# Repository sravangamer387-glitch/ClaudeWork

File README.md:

# ClaudeWork – gravity toys, electronic toys, DJ system, prototypes

| Folder | What | Start here |
|---|---|---|
| `gravity-toys/` | Research, 5 gravity-toy designs, laser-cut files, physics verification, business launch pack | `README.md` |
| `electronics-toys/` | Top-50 electronic toys for India (phases 1–6), shared audio platform firmware/hardware/enclosures | `README.md`, `wave1/README.md` |
| `dj-setup/` | Portable DJ / party system project plan (market, architecture, compliance, phased plan) | `README.md` |
| `proposals/` | The proposals that were approved and built (see `products/`) | `next-portfolio-proposal.md` |
| `products/` | Six built products (games, automata, STEM kit, tank controller, irrigation controller, LPG alarm design study) with decisions and handoff | `README.md`, `DECISIONS.md`, `HANDOFF.md` |
| `toys10/` | Ten new toys with tested engines, simulations, cut files, docs | `README.md` |
| `utility10/` | Ten utility tools (8 electronics, 2 laser-cut) with tested engines, SVG/DXF files, enclosures, docs | `README.md` |
| `prototypes/` | Build packs for ten prototypes, each under Rs 3,000, with firmware that compiles for Arduino Nano | `README.md` |

Everything is mirrored to Google Drive folders "Gravity Toys", "Electronics Toys", "DJ Setup" (documents and data tables). Source code, STL and PNG files live in this repo only.

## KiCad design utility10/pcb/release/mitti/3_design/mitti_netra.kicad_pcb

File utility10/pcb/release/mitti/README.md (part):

# MITTI-NETRA soil and structure telemetry node (ESP32-S3 + LTE-M modem socket) (rev A)

MITTI-NETRA soil and structure telemetry node (90 x 80 mm): ESP32-S3, TP4056 solar/USB charger for one Li-ion cell, 3.3 V LDO, switched socket for a SIM7080G breakout, ADXL345, HX711 strain input, soil-probe and DS18B20 inputs.

**Status: engineering release, software-verified only (ERC on the netlist, KiCad DRC, netlist cross-check, SPICE where noted). Not yet built, not reviewed by a second engineer, not certified.**

## Specification
- Board 90 x 80 mm, 2 layers, 1.6 mm FR-4, 1 oz copper, rounded corners R2.5 mm, 3 x M2.5 mounting holes, 2 fiducials.
- Rules used: min track 0.2 mm (power 0.4 mm), min clearance 0.15 mm, via 0.6/0.3 mm, GND pour on both layers, 212 stitching vias.
- Finish: ENIG recommended (HASL lead-free acceptable); green mask, white silk; IPC class 2.
- 62 parts, 41 nets.

## Circuit description
- **Charging:** solar (JST-PH 2) and USB VBUS OR-ed by SS14 diodes into a TP4056 with PROG = 2.2 k (about 0.58 A); a protected 1S Li-ion cell on JST-PH 2 (no protection IC on the board).
- **Rails:** AP2112K 3.3 V from the cell (stops regulating near 3.55 V); modem VBAT through an AO3401A high-side switch driven by an AO3400A, with 100 uF + 22 uF burst capacitors.
- **Sensors:** ADXL345 on I2C (address 0x53, INT1 wakes the MCU); HX711 (as on Gas Taraju) for a strain bridge; capacitive soil probe through 1 k + 100 nF to an ADC pin; DS18B20 on 1-Wire.

## Power
Target under 100 uA in deep sleep with the modem off (not measured); modem bursts up to about 0.5 A while transmitting.

## Verification
| Check | Result |
|---|---|
| Electrical rule check on the netlist (own ERC: unconnected pins, single-pin nets, output conflicts, unpowered supplies, symbol/footprint pin match) | 0 errors, 0 warnings |
| KiCad DRC | 0 errors, 0 warnings; unconnected pads: 0 |
| Schematic netlist equals PCB netlist | NO: {"[('D2', '2'), ('J1', 'A4'), ('J1', 'A9')]...": 'only in PCB', "[('D2', '1'), ('J1', 'A4'), ('J1', 'A9')]...": 'only in schematic', "[('C1', '1'), ('D1', '1'), ('D2', '1')]...": 'only in PCB', "[('D1', '1'), ('J2', '1')]...": 'only in schematic', "[('D1', '2'), ('J2', '1')]...": 'only in PCB', "[('C1', '1'), ('D1', '2'), ('D2', '2')]...": 'only in schematic'} |
| Router failures | 0 |
| 3D STEP export | yes |
| Independent Gerber parse (gerbonara): layers parsed, outline size equals the design | 9 layers, outline [90.1, 80.1] mm, match |

Enclosure (prototype shell for 3D printing): outer 95.2 x 85.2 x 20.6 mm, collision/opening check: pass

## Bill of materials
| Ref | Value | Footprint | Manufacturer part | LCSC # | LCSC status |
|---|---|---|---|---|---|
| U1 | ESP32-S3-WROOM-1-N8 | ESP32-S3-WROOM-1 | ESP32-S3-WROOM-1-N8 | C2913198 | verified |
| C37 | 100n | C_0603_1608Metric | Samsung CL10B104KB8NNNC 0603 100nF X7R 50V | C1591 | verified |
| C38 | 10u | C_0805_2012Metric | 0805 10uF X5R | C15850 | verified |
| R42 | 10k | R_0603_1608Metric | 0603 10k 1% | C25804 | verified |
| C39 | 1u | C_0603_1608Metric | 0603 1uF X7R | C15849 | verified |
| SW2 | Reset (EN) | SW_SPST_B3U-1000P | Omron B3U-1000P | C231329 | verified |
| SW3 | Boot (IO0) | SW_SPST_B3U-1000P | Omron B3U-1000P | C231329 | verified |
| J1 | USB-C (charge + program) | USB_C_Receptacle_HRO_TYPE-C-31-M-12 | TYPE-C-31-M-12 | C165948 | verified |
| R43 | 5.1k | R_0603_1608Metric | 0603 5.1k 1% | C23186 | verified |
| R44 | 5.1k | R_0603_1608Metric | 0603 5.1k 1% | C23186 | verified |
| J2 | Solar panel 5-6 V | JST_PH_B2B-PH-K_1x02_P2.00mm_Vertical | JST B2B-PH-K-S(LF)(SN) | C131337 | verified |
| D1 | SS14 | D_SMA | SS14 | C84343 | verified |
| D2 | SS14 | D_SMA | SS14 | C84343 | verified |
| C1 | 10u | C_0805_2012Metric | 0805 10uF X5R | C15850 | verified |
| U4 | TP4056 | HSOP-8-1EP_3.9x4.9mm_P1.27mm_EP2.41x3.1mm | TPOWER TP4056 | C382139 | verified |
| R1 | 2.2k | R_0603_1608Metric | 0603 2.2k 1% | C4190 | verified |
| C2 | 10u | C_0805_2012Metric | 0805 10uF X5R | C15850 | verified |
| D3 | Red | LED_0603_1608Metric | Hubei KENTO KT-0603R red (Everlight 19-217 was out of stock) | C2286 | verified |
| R2 | 1k | R_0603_1608Metric | 0603 1k 1% | C21190 | verified |
| D4 | Green | LED_0603_1608Metric | Hubei KENTO KT-0603YG yellow-green 570 nm, Vf about 2 V (lights well from 3.3 V with 1 k; the Everlight 19-217 green was out of stock) | C2289 | verified |
| R3 | 1k | R_0603_1608Metric | 0603 1k 1% | C21190 | verified |
| J3 | Li-ion cell (protected!) | JST_PH_B2B-PH-K_1x02_P2.00mm_Vertical | JST B2B-PH-K-S(LF)(SN) | C131337 | verified |
| U3 | AP2112K-3.3 | SOT-23-5 | AP2112K-3.3TRG1 | C51118 | verified |
| C3 | 1u | C_0603_1608Metric | 0603 1uF X7R | C15849 | verified |
| C4 | 10u | C_0805_2012Metric | 0805 10uF X5R | C15850 | verified |
| R4 | 330k | R_0603_1608Metric | UNI-ROYAL 0603WAF3303T5E | C23137 | verified |
| R5 | 330k | R_0603_1608Metric | UNI-ROYAL 0603WAF3303T5E | C23137 | verified |
| C5 | 100n | C_0603_1608Metric | Samsung CL10B104KB8NNNC 0603 100nF X7R 50V | C1591 | verified |
| Q1 | AO3401A | SOT-23 | AO3401A | C15127 | verified |
| R6 | 100k | R_0603_1608Metric | 0603 100k 1% | C25803 | verified |
| Q2 | AO3400A | SOT-23 | AO3400A | C20917 | verified |
| R7 | 100 | R_0603_1608Metric | UNI-ROYAL 0603WAF1000T5E | C22775 | verified |
| R8 | 100k | R_0603_1608Metric | 0603 100k 1% | C25803 | verified |
| C6 | 100u/35V | CP_Elec_6.3x7.7 | Lelon VZH101M1VTR-0607 | C176683 | verified |
| C7 | 22u/10V | C_0805_2012Metric | Samsung CL21A226MPQNNNE | C29277 | verified |
| J6 | Cellular modem (SIM7080G breakout) | PinHeader_2x03_P2.54mm_Vertical | HCTL PZ254-2-03-Z-8.5 | C2894964 | verified |
| U5 | ADXL345 | LGA-14_3x5mm_P0.8mm_LayoutBorder1x6y | ADXL345BCCZ-RL7 | C9667 | verified |
| C8 | 100n | C_0603_1608Metric | Samsung CL10B104KB8NNNC 0603 100nF X7R 50V | C1591 | verified |
| C9 | 100n | C_0603_1608Metric | Samsung CL10B104KB8NNNC 0603 100nF X7R 50V | C1591 | verified |
| R9 | 4.7k | R_0603_1608Metric | 0603 4.7k 1% | C23162 | verified |
| R10 | 4.7k | R_0603_1608Metric | 0603 4.7k 1% | C23162 | verified |
| U2 | HX711 | SOIC-16_3.9x9.9mm_P1.27mm | HX711 | C43656 | verified |
| R11 | 100 | R_0603_1608Metric | UNI-ROYAL 0603WAF1000T5E | C22775 | verified |
| C10 | 100n | C_0603_1608Metric | Samsung CL10B104KB8NNNC 0603 100nF X7R 50V | C1591 | verified |
| C11 | 100n | C_0603_1608Metric | Samsung CL10B104KB8NNNC 0603 100nF X7R 50V | C1591 | verified |
| C12 | 100n | C_0603_1608Metric | Samsung CL10B104KB8NNNC 0603 100nF X7R 50V | C1591 | verified |
| C13 | 10u | C_0805_2012Metric | 0805 10uF X5R | C15850 | verified |
| R12 | 100 | R_0603_1608Metric | UNI-ROYAL 0603WAF1000T5E | C22775 | verified |
| C14 | 100n | C_0603_1608Metric | Samsung CL10B104KB8NNNC 0603 100nF X7R 50V | C1591 | verified |
| C15 | 100n | C_0603_1608Metric | Samsung CL10B104KB8NNNC 0603 100nF X7R 50V | C1591 | verified |
| J4 | Strain-gauge bridge E+ E- A+ A- | JST_PH_B4B-PH-K_1x04_P2.00mm_Vertical | JST B4B-PH-K-S(LF)(SN) | C131334 | verified |
| J5 | Soil probe (capacitive, 3.3 V) | JST_PH_B3B-PH-K_1x03_P2.00mm_Vertical | JST B3B-PH-K-S(LF)(SN) | C131339 | verified |
| J7 | DS18B20 temp | JST_PH_B3B-PH-K_1x03_P2.00mm_Vertical | JST B3B-PH-K-S | C131339 | verified |
| R13 | 4.7k | R_0603_1608Metric | 0603 4.7k 1% | C23162 | verified |
| R15 | 1k | R_0603_1608Metric | 0603 1k 1% | C21190 | verified |
| C16 | 100n | C_0603_1608Metric | Samsung CL10B104KB8NNNC 0603 100nF X7R 50V | C1591 | verified |
| D5 | Green | LED_0603_1608Metric | Hubei KENTO KT-0603YG yellow-green 570 nm, Vf about 2 V (lights well from 3.3 V with 1 k; the Everlight 19-217 green was out of stock) | C2289 | verified |
| R14 | 1k | R_0603_1608Metric | 0603 1k 1% | C21190 | verified |
| J8 | UART flash/debug (USB-serial adapter) | JST_PH_B3B-PH-K_1x03_P2.00mm_Vertical | JST B3B-PH-K-S(LF)(SN) | C131339 | verified |
| TP1 | TP | TestPoint_Pad_D1.5mm |  |  |  |
| TP2 | TP | TestPoint_Pad_D1.5mm |  |  |  |
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
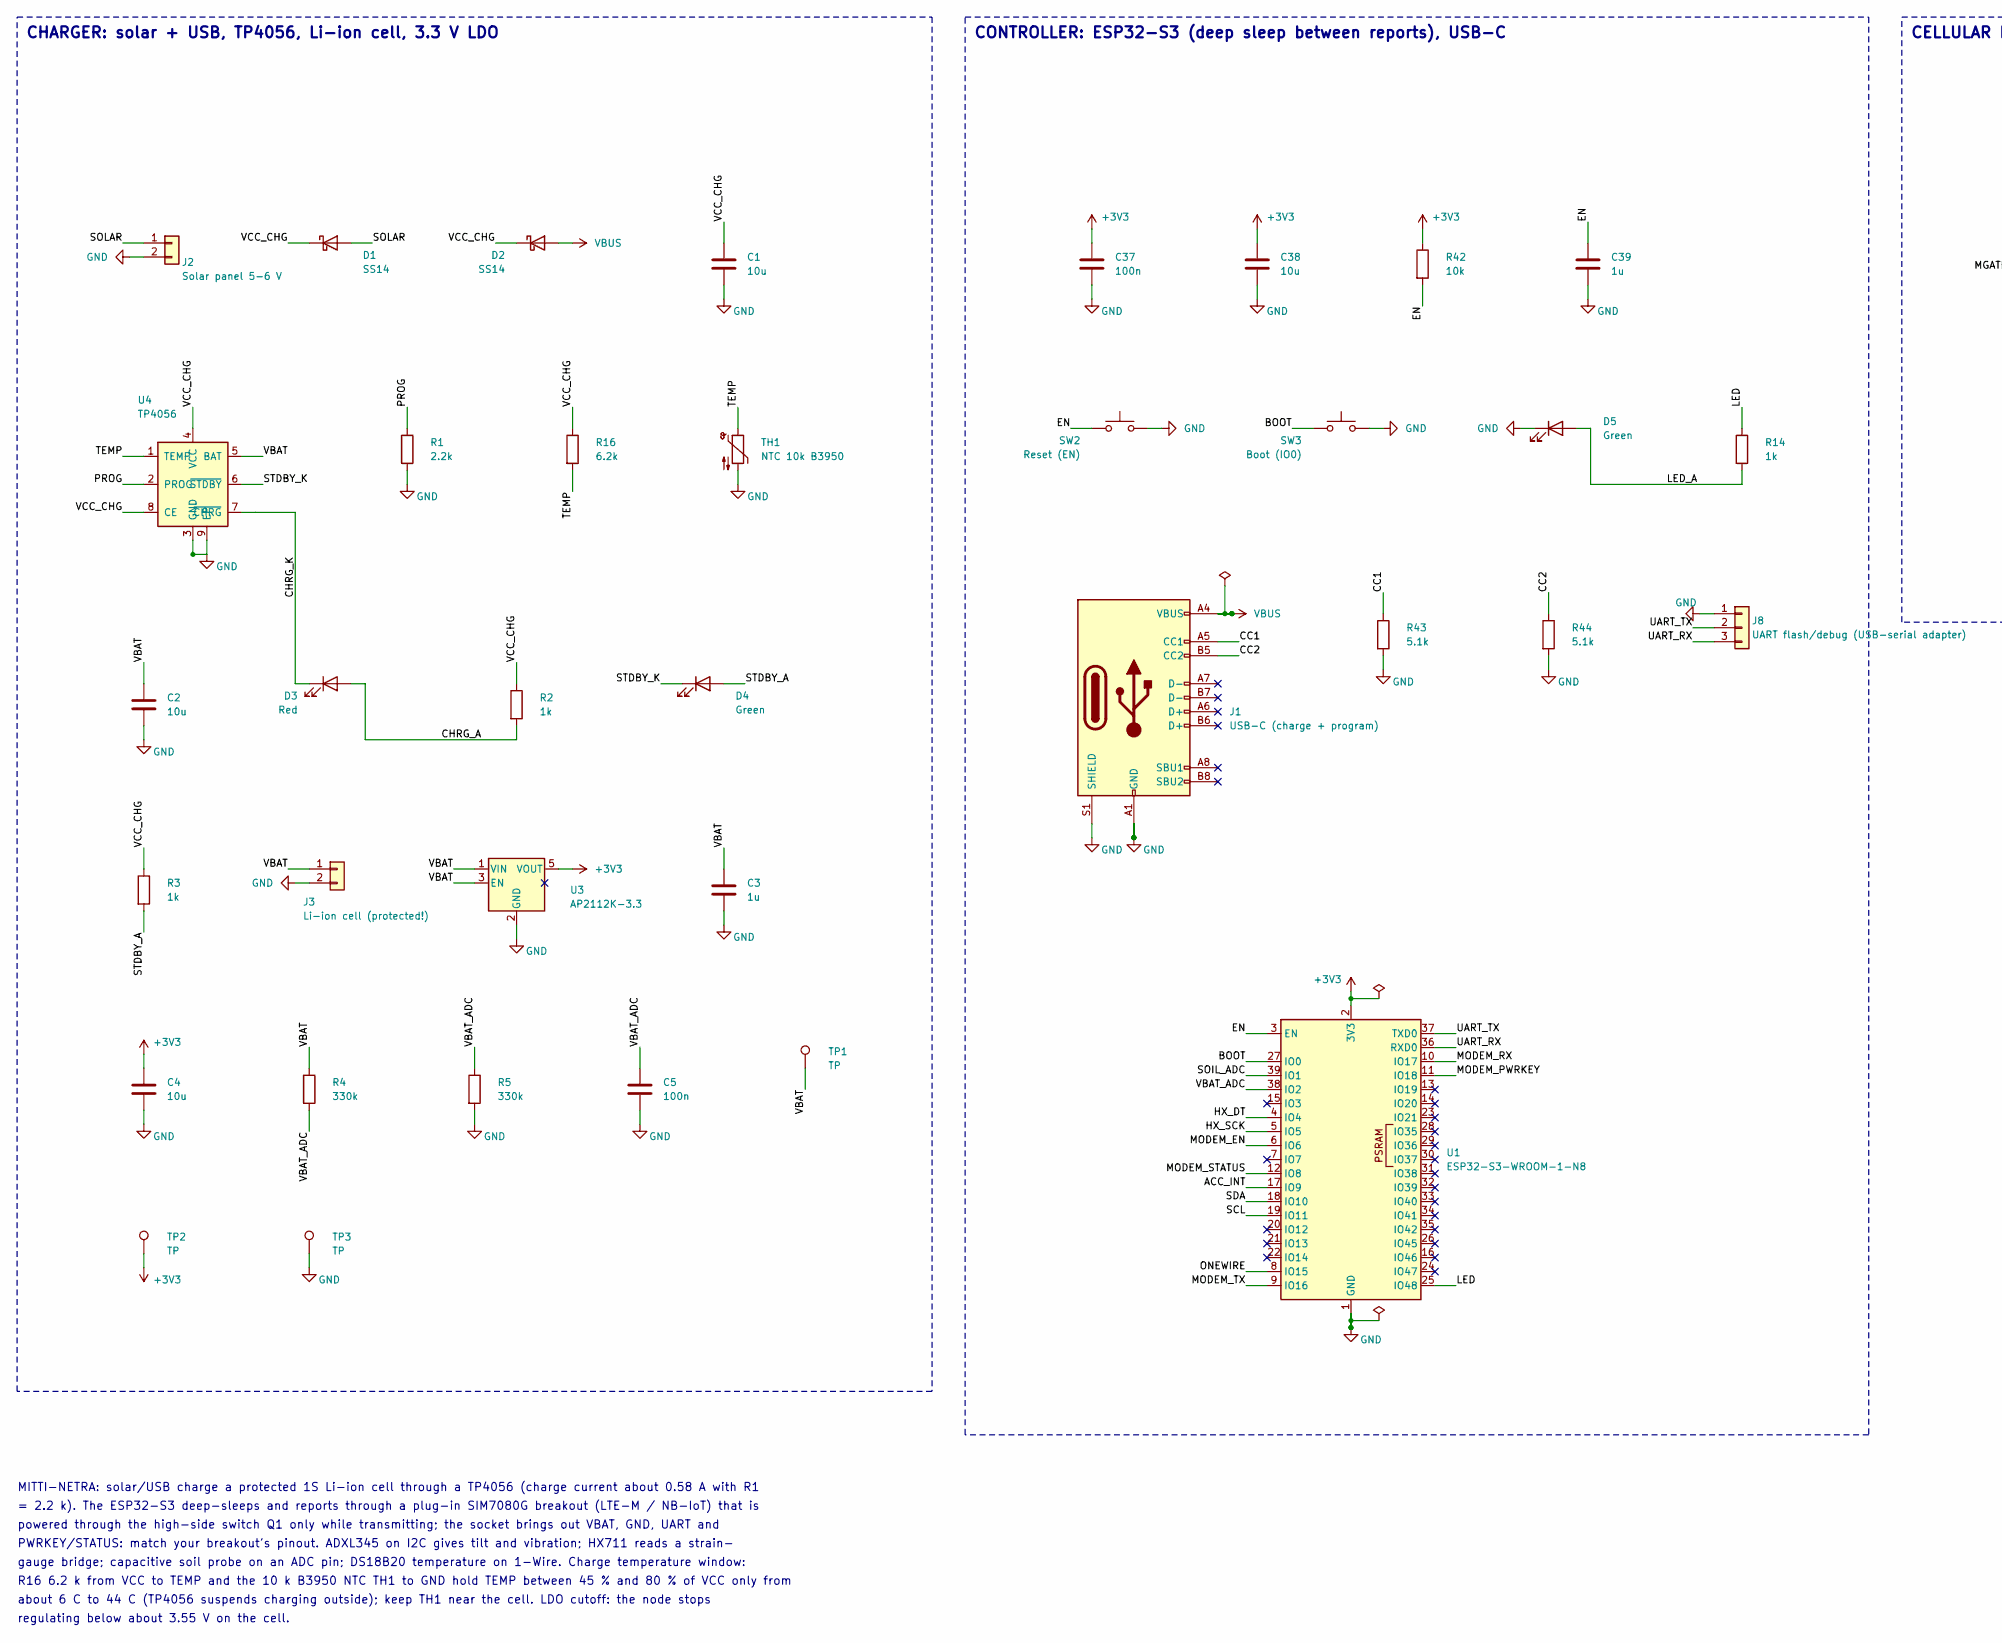
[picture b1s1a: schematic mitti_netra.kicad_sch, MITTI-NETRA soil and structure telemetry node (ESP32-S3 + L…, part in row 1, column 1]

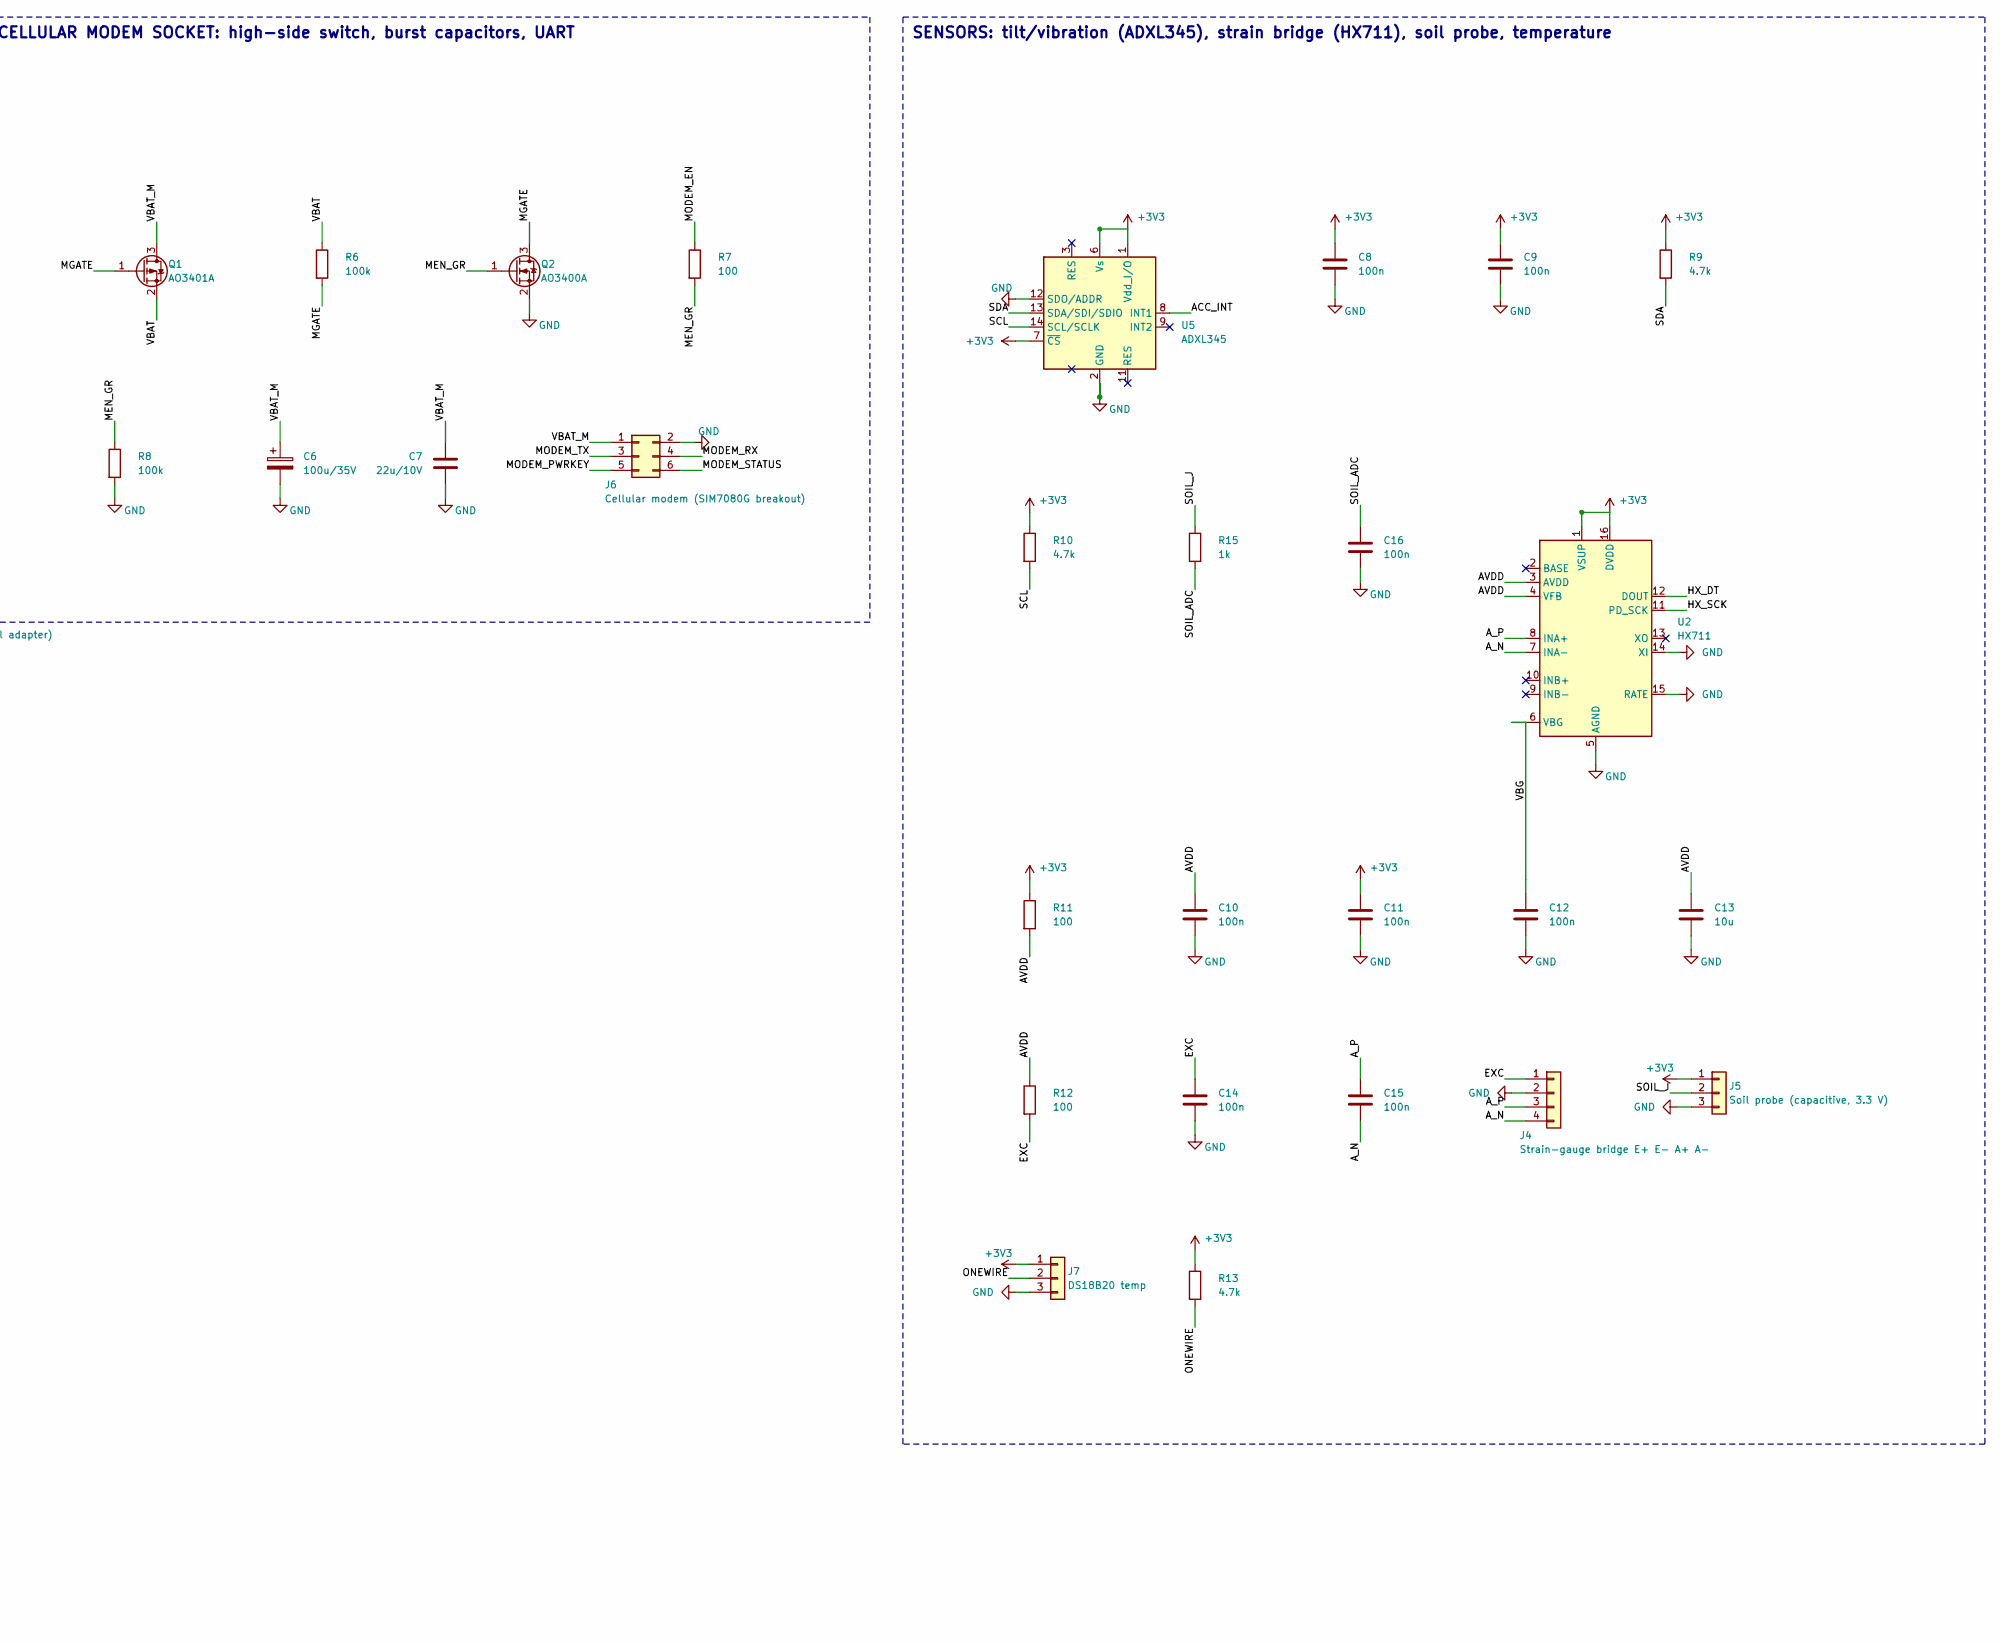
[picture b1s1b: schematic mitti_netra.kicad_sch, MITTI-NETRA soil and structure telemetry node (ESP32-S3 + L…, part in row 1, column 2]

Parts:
C1, C2, C4, C13, C38: 10u; C_0805_2012Metric
C3, C39: 1u; C_0603_1608Metric
C5, C8, C9, C10, C11, C12, C14, C15, C16, C37: 100n; C_0603_1608Metric
C6: 100u/35V; CP_Elec_6.3x7.7
C7: 22u/10V; C_0805_2012Metric
D1, D2: SS14; D_SMA
D3: Red; LED_0603_1608Metric
D4, D5: Green; LED_0603_1608Metric
J1: USB-C (charge + program); USB_C_Receptacle_HRO_TYPE-C-31-M-12
J2: Solar panel 5-6 V; JST_PH_B2B-PH-K_1x02_P2.00mm_Vertical
J3: Li-ion cell (protected!); JST_PH_B2B-PH-K_1x02_P2.00mm_Vertical
J4: Strain-gauge bridge E+ E- A+ A-; JST_PH_B4B-PH-K_1x04_P2.00mm_Vertical
J5: Soil probe (capacitive, 3.3 V); JST_PH_B3B-PH-K_1x03_P2.00mm_Vertical
J6: Cellular modem (SIM7080G breakout); PinHeader_2x03_P2.54mm_Vertical
J7: DS18B20 temp; JST_PH_B3B-PH-K_1x03_P2.00mm_Vertical
J8: UART flash/debug (USB-serial adapter); JST_PH_B3B-PH-K_1x03_P2.00mm_Vertical
Q1: AO3401A; SOT-23
Q2: AO3400A; SOT-23
R1: 2.2k; R_0603_1608Metric
R2, R3, R14, R15: 1k; R_0603_1608Metric
R4, R5: 330k; R_0603_1608Metric
R6, R8: 100k; R_0603_1608Metric
R7, R11, R12: 100; R_0603_1608Metric
R9, R10, R13: 4.7k; R_0603_1608Metric
R16: 6.2k; R_0603_1608Metric
R42: 10k; R_0603_1608Metric
R43, R44: 5.1k; R_0603_1608Metric
SW2: Reset (EN); SW_SPST_B3U-1000P
SW3: Boot (IO0); SW_SPST_B3U-1000P
TH1: NTC 10k B3950; R_0805_2012Metric
TP1, TP2, TP3: TP; TestPoint_Pad_D1.5mm
U1: ESP32-S3-WROOM-1-N8; ESP32-S3-WROOM-1
U2: HX711; SOIC-16_3.9x9.9mm_P1.27mm
U3: AP2112K-3.3; SOT-23-5
U4: TP4056; HSOP-8-1EP_3.9x4.9mm_P1.27mm_EP2.41x3.1mm
U5: ADXL345; LGA-14_3x5mm_P0.8mm_LayoutBorder1x6y

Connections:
+3V3: C4.1, C8.1, C9.1, C11.1, C37.1, C38.1, J5.1, J7.1, R9.1, R10.1, R11.1, R13.1, R42.1, TP2.1, U1.2 (3V3), U2.1 (VSUP), U2.16 (DVDD), U3.5 (VOUT), U5.1 (Vdd_I/O), U5.6 (Vs), U5.7 (~CS)
ACC_INT: U1.17 (IO9), U5.8 (INT1)
AVDD: C10.1, C13.1, R11.2, R12.1, U2.3 (AVDD), U2.4 (VFB)
A_N: C15.2, J4.4, U2.7 (INA-)
A_P: C15.1, J4.3, U2.8 (INA+)
BOOT: SW3.1, U1.27 (IO0)
CC1: J1.A5 (CC1), R43.1
CC2: J1.B5 (CC2), R44.1
CHRG_A: D3.2 (A), R2.2
CHRG_K: D3.1 (K), U4.7 (~CHRG)
EN: C39.1, R42.2, SW2.1, U1.3 (EN)
EXC: C14.1, J4.1, R12.2
GND: C1.2, C2.2, C3.2, C4.2, C5.2, C6.2, C7.2, C8.2, C9.2, C10.2, C11.2, C12.2, C13.2, C14.2, C16.2, C37.2, C38.2, C39.2, D5.1 (K), J1.A1 (GND), J1.A12 (GND), J1.B1 (GND), J1.B12 (GND), J1.S1 (SHIELD), J2.2, J3.2, J4.2, J5.3, J6.2, J7.3, J8.1, Q2.2 (S), R1.2, R5.2, R8.2, R43.2, R44.2, SW2.2, SW3.2, TH1.2, TP3.1, U1.1 (GND), U1.40 (GND), U1.41 (GND), U2.5 (AGND), U2.14 (XI), U2.15 (RATE), U3.2 (GND), U4.3 (GND), U4.9 (EP), U5.2 (GND), U5.4 (GND), U5.5 (GND), U5.12 (SDO/ADDR)
HX_DT: U1.4 (IO4), U2.12 (DOUT)
HX_SCK: U1.5 (IO5), U2.11 (PD_SCK)
LED: R14.1, U1.25 (IO48)
LED_A: D5.2 (A), R14.2
MEN_GR: Q2.1 (G), R7.2, R8.1
MGATE: Q1.1 (G), Q2.3 (D), R6.2
MODEM_EN: R7.1, U1.6 (IO6)
MODEM_PWRKEY: J6.5, U1.11 (IO18)
MODEM_RX: J6.4, U1.10 (IO17)
MODEM_STATUS: J6.6, U1.12 (IO8)
MODEM_TX: J6.3, U1.9 (IO16)
ONEWIRE: J7.2, R13.2, U1.8 (IO15)
PROG: R1.1, U4.2 (PROG)
SCL: R10.2, U1.19 (IO11), U5.14 (SCL/SCLK)
SDA: R9.2, U1.18 (IO10), U5.13 (SDA/SDI/SDIO)
SOIL_ADC: C16.1, R15.2, U1.39 (IO1)
SOIL_J: J5.2, R15.1
SOLAR: D1.2 (A), J2.1
STDBY_A: D4.2 (A), R3.2
STDBY_K: D4.1 (K), U4.6 (~STDBY)
TEMP: R16.2, TH1.1, U4.1 (TEMP)
UART_RX: J8.3, U1.36 (RXD0)
UART_TX: J8.2, U1.37 (TXD0)
VBAT: C2.1, C3.1, J3.1, Q1.2 (S), R4.1, R6.1, TP1.1, U3.1 (VIN), U3.3 (EN), U4.5 (BAT)
VBAT_ADC: C5.1, R4.2, R5.1, U1.38 (IO2)
VBAT_M: C6.1, C7.1, J6.1, Q1.3 (D)
VBG: C12.1, U2.6 (VBG)
VBUS: D2.2 (A), J1.A4 (VBUS), J1.A9 (VBUS), J1.B4 (VBUS), J1.B9 (VBUS)
VCC_CHG: C1.1, D1.1 (K), D2.1 (K), R2.1, R3.1, R16.1, U4.4 (VCC), U4.8 (CE)

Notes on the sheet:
CHARGER: solar + USB, TP4056, Li-ion cell, 3.3 V LDO
CONTROLLER: ESP32-S3 (deep sleep between reports), USB-C
CELLULAR MODEM SOCKET: high-side switch, burst capacitors, UART
SENSORS: tilt/vibration (ADXL345), strain bridge (HX711), soil probe, temperature
MITTI-NETRA: solar/USB charge a protected 1S Li-ion cell through a TP4056 (charge current about 0.58 A with R1
= 2.2 k). The ESP32-S3 deep-sleeps and reports through a plug-in SIM7080G breakout (LTE-M / NB-IoT) that is
powered through the high-side switch Q1 only while transmitting; the socket brings out VBAT, GND, UART and
PWRKEY/STATUS: match your breakout's pinout. ADXL345 on I2C gives tilt and vibration; HX711 reads a strain-
gauge bridge; capacitive soil probe on an ADC pin; DS18B20 temperature on 1-Wire. Charge temperature window:
R16 6.2 k from VCC to TEMP and the 10 k B3950 NTC TH1 to GND hold TEMP between 45 % and 80 % of VCC only from
about 6 C to 44 C (TP4056 suspends charging outside); keep TH1 near the cell. LDO cutoff: the node stops
regulating below about 3.55 V on the cell.

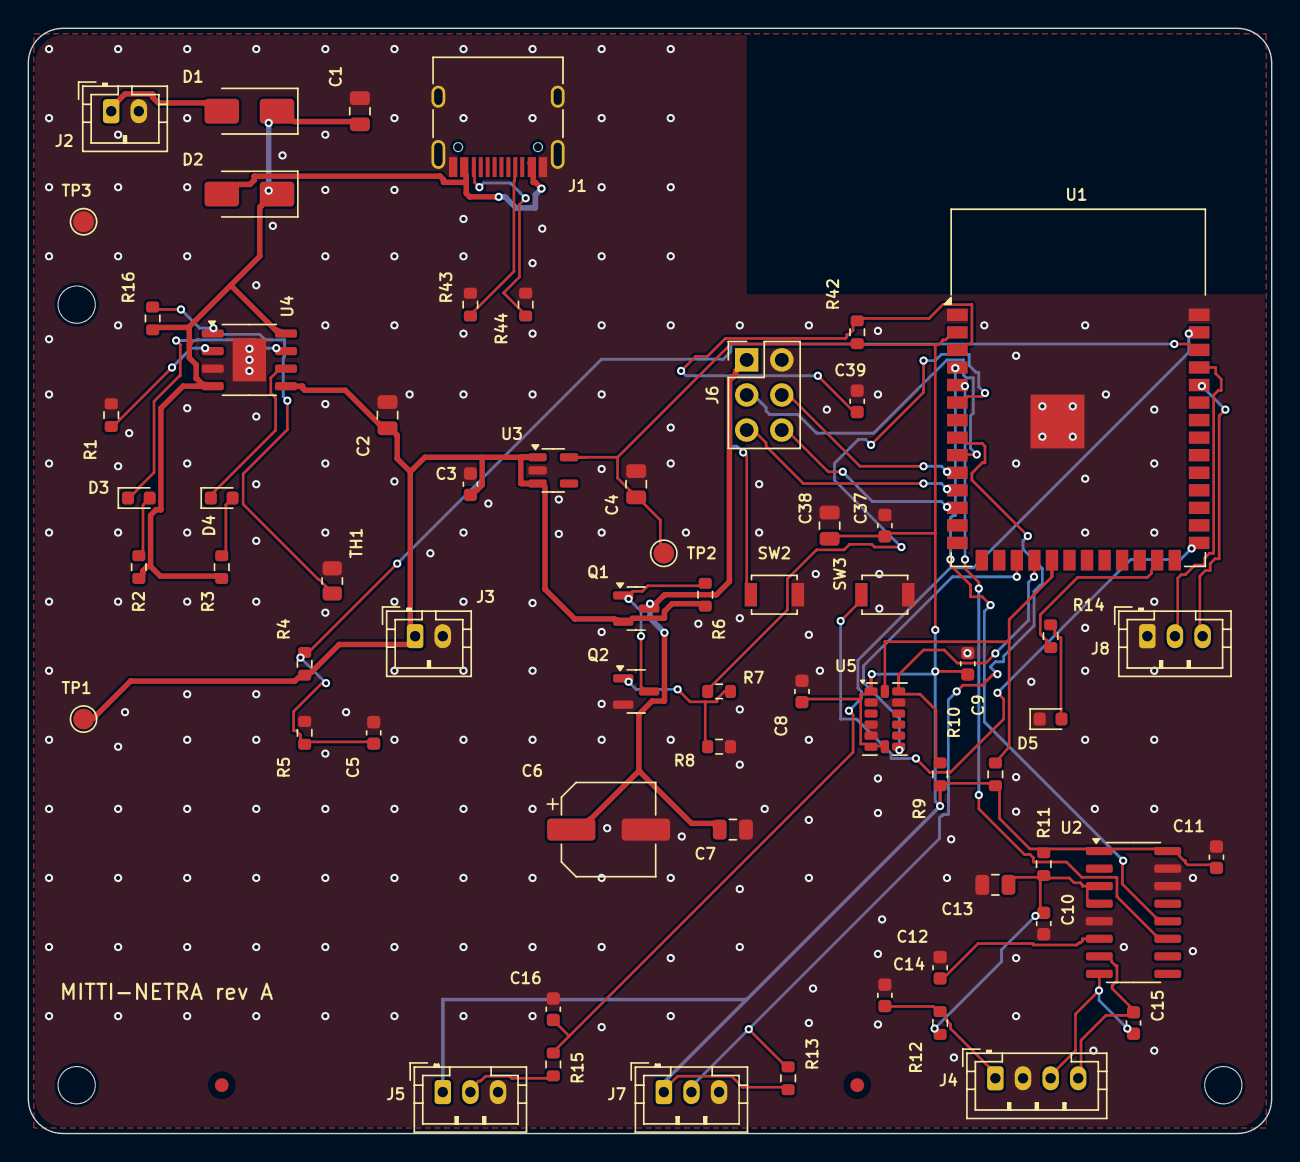
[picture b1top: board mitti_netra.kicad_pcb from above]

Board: 2 copper layers, 90.0 x 80.0 mm, 69 parts (0 on the bottom side), 42 nets.

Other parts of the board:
FID1, FID2: Fiducial; Fiducial_1mm_Mask2mm
H1, H2, H3: M2.5; MountingHole_2.7mm_M2.5

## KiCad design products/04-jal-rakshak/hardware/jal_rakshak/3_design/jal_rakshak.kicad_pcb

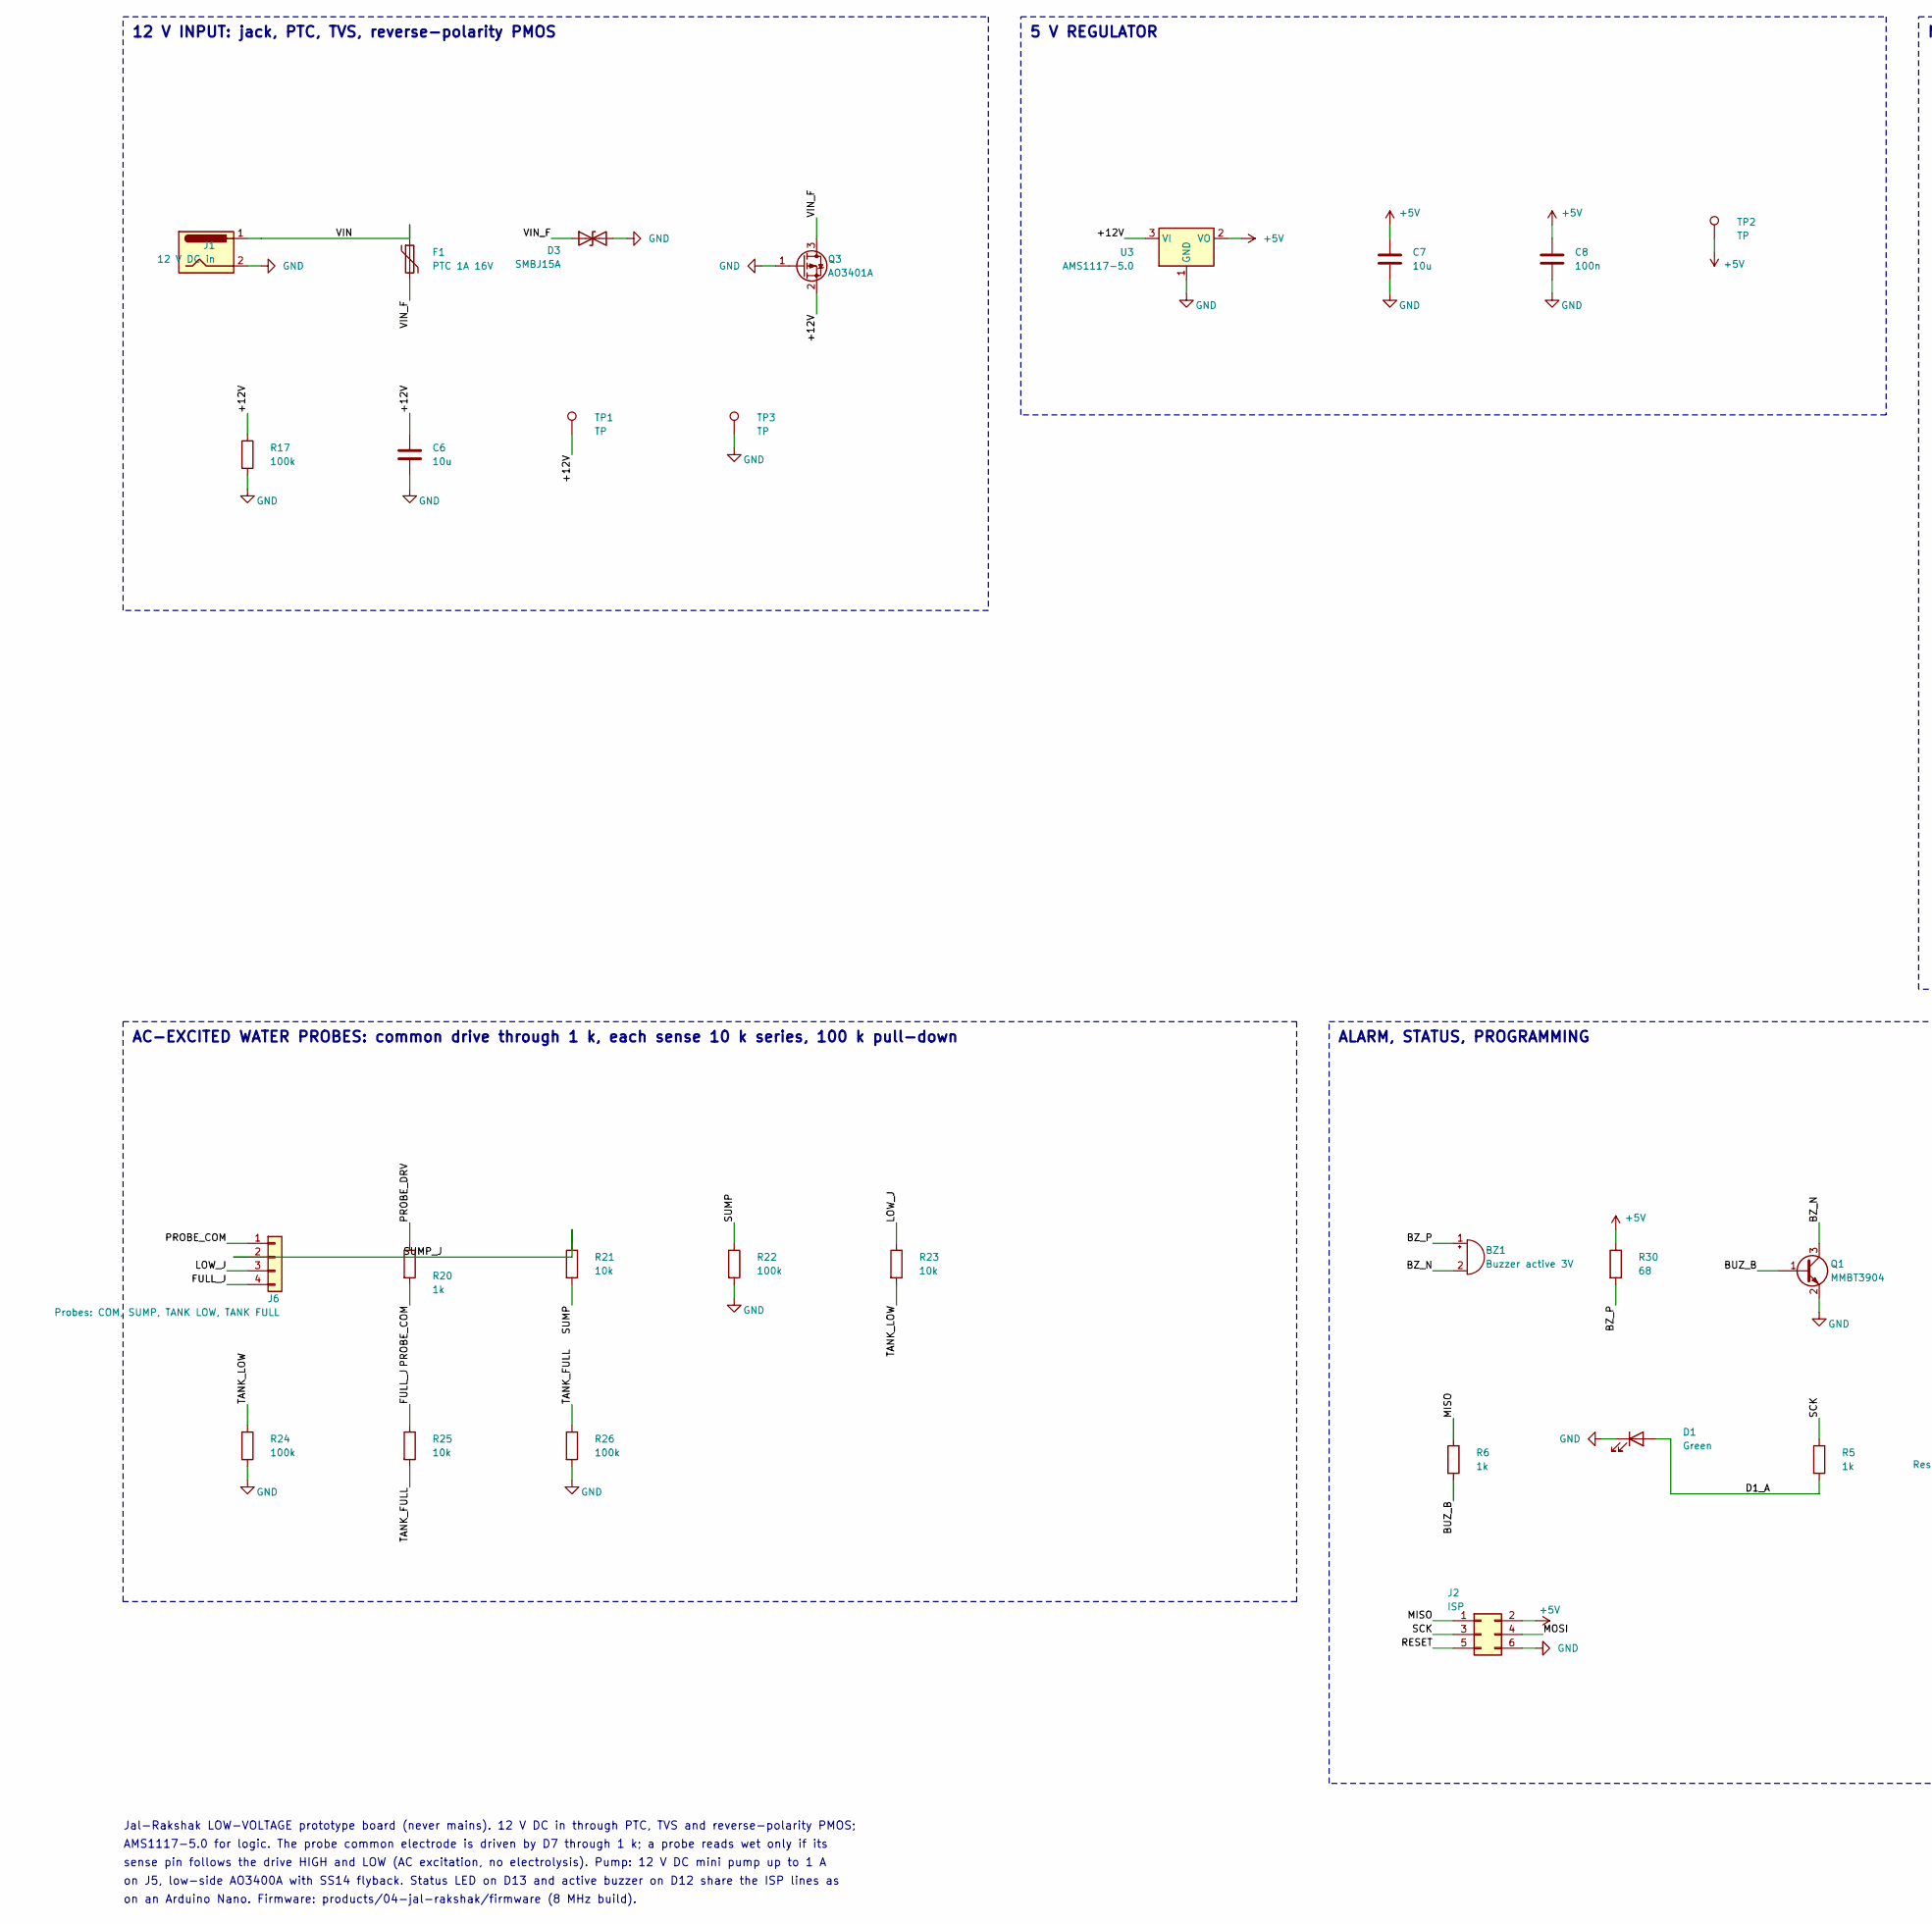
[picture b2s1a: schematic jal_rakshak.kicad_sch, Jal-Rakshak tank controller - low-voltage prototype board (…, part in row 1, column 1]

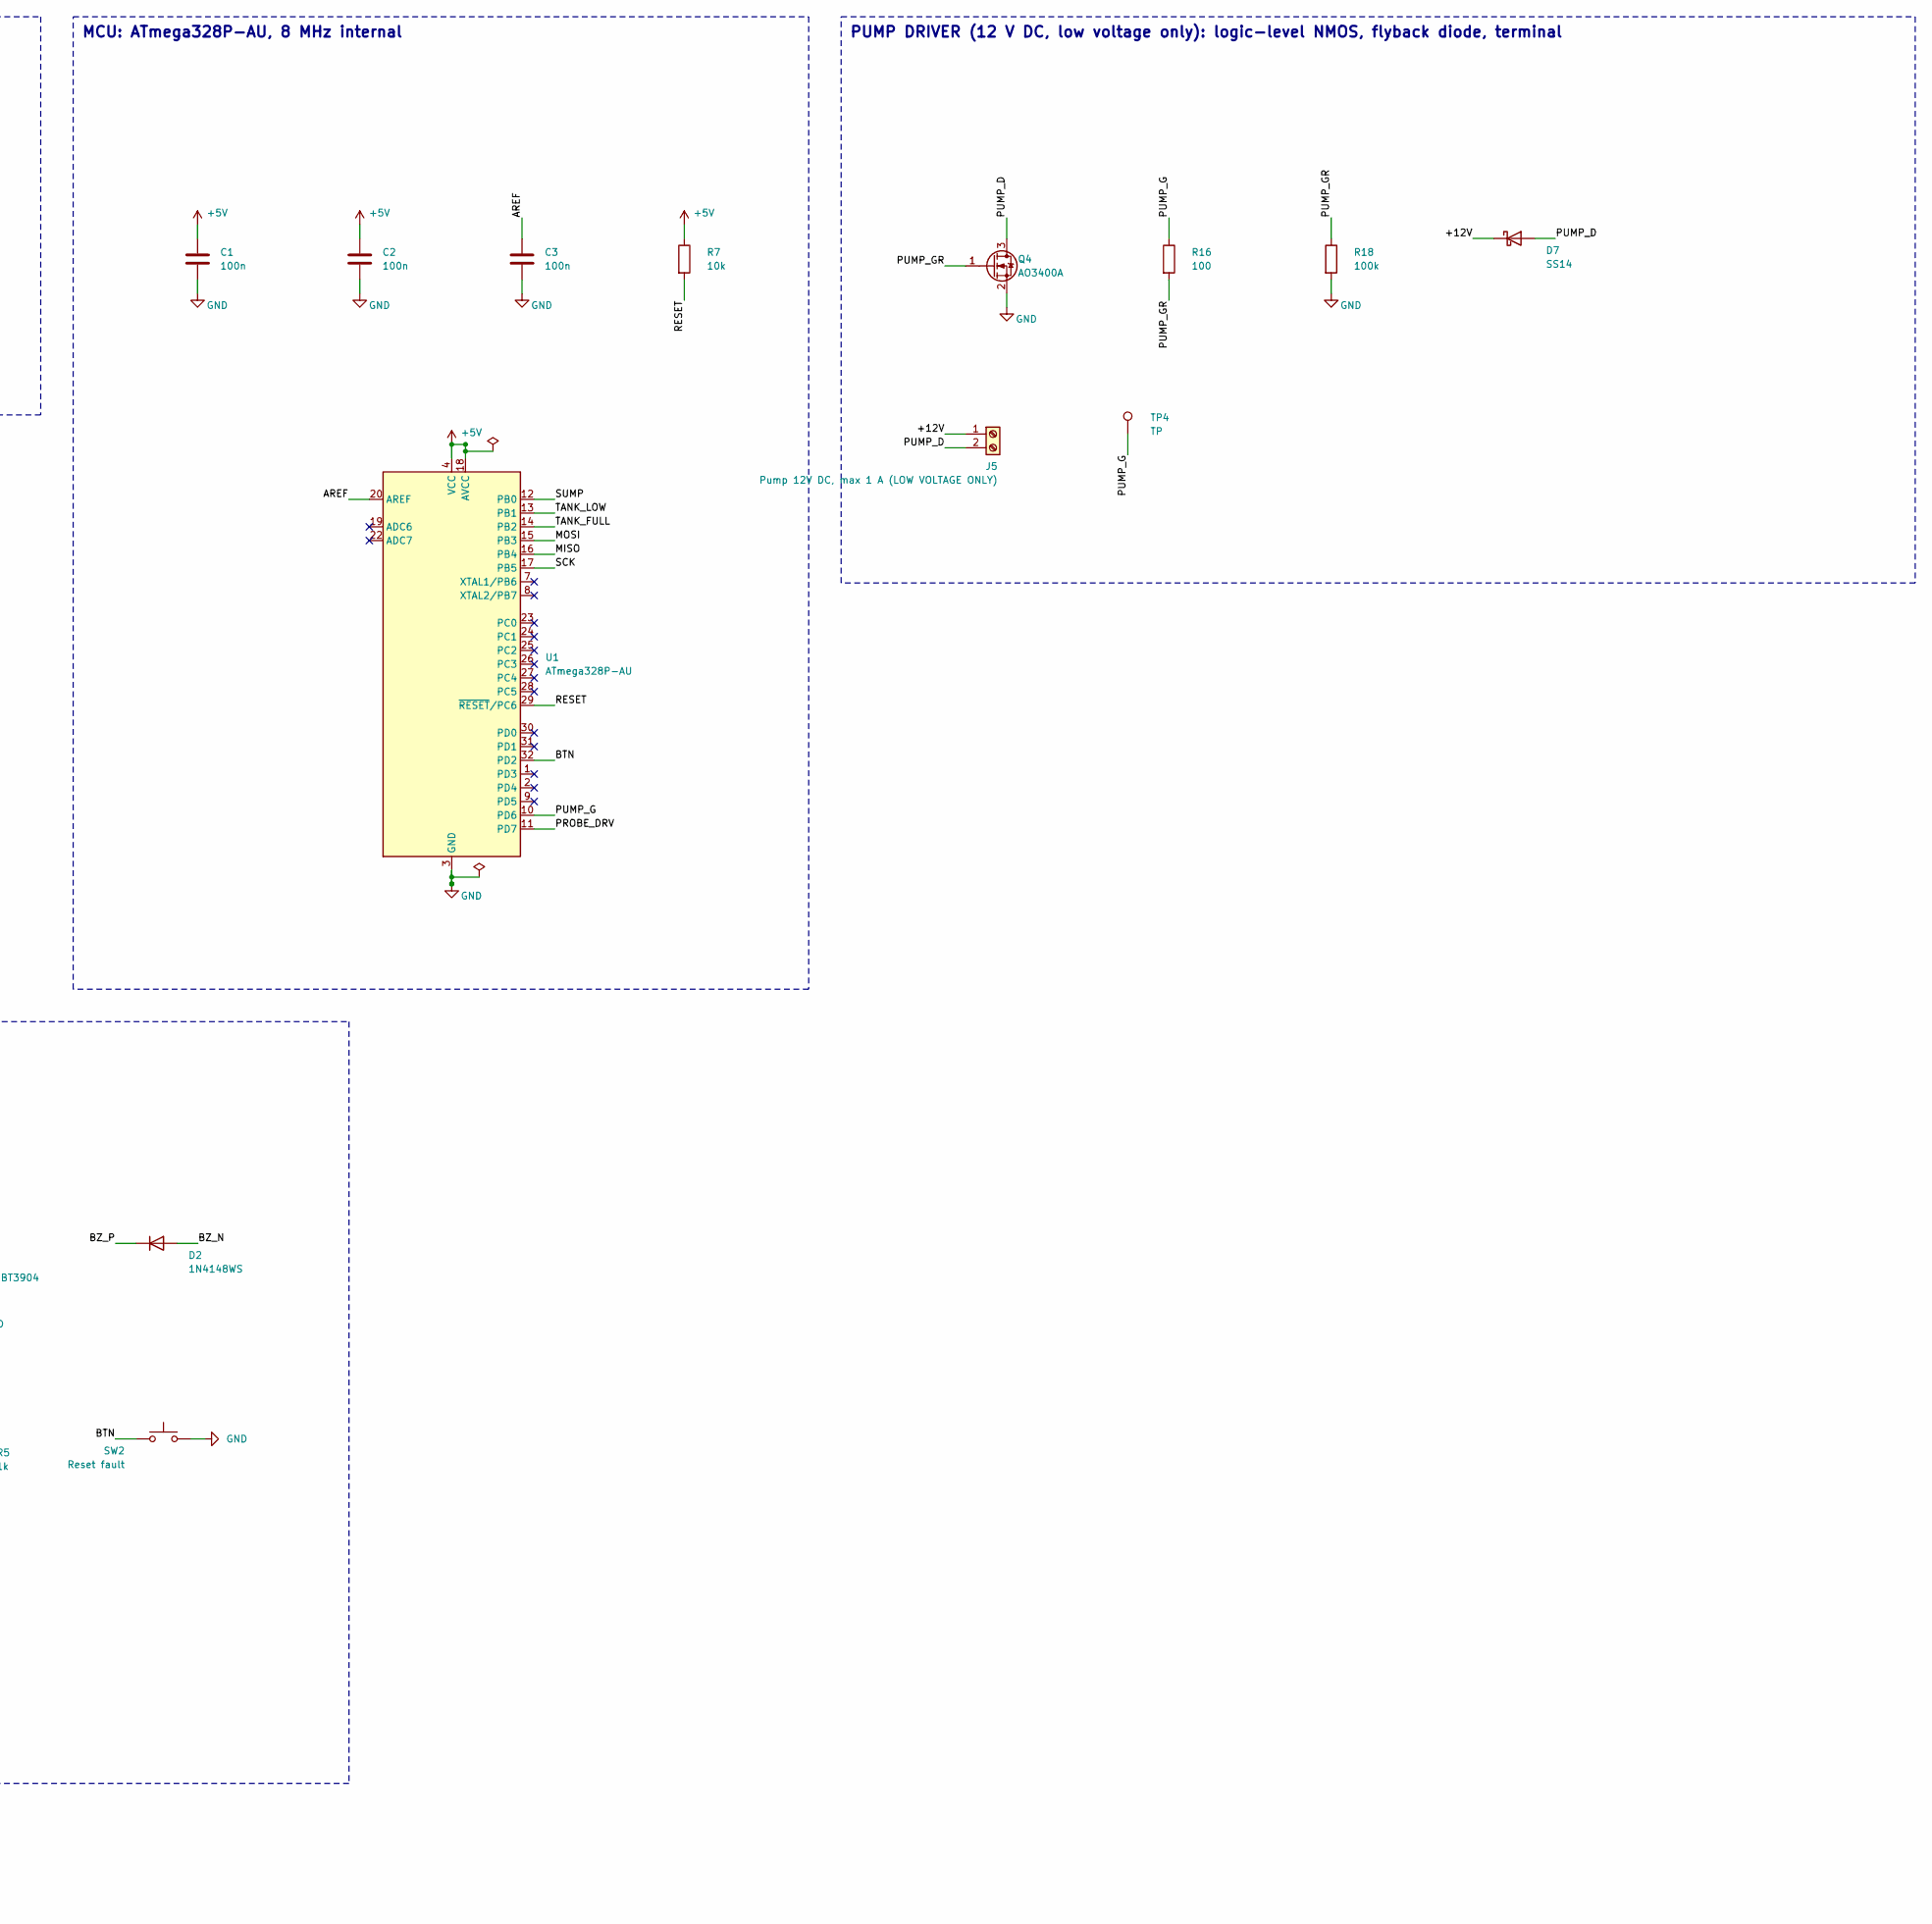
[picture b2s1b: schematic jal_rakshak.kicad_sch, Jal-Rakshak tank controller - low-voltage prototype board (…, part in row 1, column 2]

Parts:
BZ1: Buzzer active 3V; Buzzer_12x9.5RM7.6
C1, C2, C3, C8: 100n; C_0603_1608Metric
C6, C7: 10u; C_0805_2012Metric
D1: Green; LED_0603_1608Metric
D2: 1N4148WS; D_SOD-323
D3: SMBJ15A; D_SMB
D7: SS14; D_SMA
F1: PTC 1A 16V; Fuse_1812_4532Metric
J1: 12 V DC in; BarrelJack_CUI_PJ-063AH_Horizontal
J2: ISP; PinHeader_2x03_P2.54mm_Vertical
J5: Pump 12V DC, max 1 A (LOW VOLTAGE ONLY); TerminalBlock_bornier-2_P5.08mm
J6: Probes: COM, SUMP, TANK LOW, TANK FULL; JST_PH_B4B-PH-K_1x04_P2.00mm_Vertical
Q1: MMBT3904; SOT-23
Q3: AO3401A; SOT-23
Q4: AO3400A; SOT-23
R5, R6, R20: 1k; R_0603_1608Metric
R7, R21, R23, R25: 10k; R_0603_1608Metric
R16: 100; R_0603_1608Metric
R17, R18, R22, R24, R26: 100k; R_0603_1608Metric
R30: 68; R_0603_1608Metric
SW2: Reset fault; SW_SPST_B3U-1000P
TP1, TP2, TP3, TP4: TP; TestPoint_Pad_D1.5mm
U1: ATmega328P-AU; TQFP-32_7x7mm_P0.8mm
U3: AMS1117-5.0; SOT-223-3_TabPin2

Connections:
+5V: C1.1, C2.1, C7.1, C8.1, J2.2, R7.1, R30.1, TP2.1, U1.4 (VCC), U1.6 (VCC), U1.18 (AVCC), U3.2 (VO)
+12V: C6.1, D7.1 (K), J5.1, Q3.2 (S), R17.1, TP1.1, U3.3 (VI)
AREF: C3.1, U1.20 (AREF)
BTN: SW2.1, U1.32 (PD2)
BUZ_B: Q1.1 (B), R6.2
BZ_N: BZ1.2 (-), D2.2 (A), Q1.3 (C)
BZ_P: BZ1.1 (+), D2.1 (K), R30.2
D1_A: D1.2 (A), R5.2
FULL_J: J6.4, R25.1
GND: C1.2, C2.2, C3.2, C6.2, C7.2, C8.2, D1.1 (K), D3.2 (A2), J1.2, J2.6, Q1.2 (E), Q3.1 (G), Q4.2 (S), R17.2, R18.2, R22.2, R24.2, R26.2, SW2.2, TP3.1, U1.3 (GND), U1.5 (GND), U1.21 (GND), U3.1 (GND)
LOW_J: J6.3, R23.1
MISO: J2.1, R6.1, U1.16 (PB4)
MOSI: J2.4, U1.15 (PB3)
PROBE_COM: J6.1, R20.2
PROBE_DRV: R20.1, U1.11 (PD7)
PUMP_D: D7.2 (A), J5.2, Q4.3 (D)
PUMP_G: R16.1, TP4.1, U1.10 (PD6)
PUMP_GR: Q4.1 (G), R16.2, R18.1
RESET: J2.5, R7.2, U1.29 (~RESET/PC6)
SCK: J2.3, R5.1, U1.17 (PB5)
SUMP: R21.2, R22.1, U1.12 (PB0)
SUMP_J: J6.2, R21.1
TANK_FULL: R25.2, R26.1, U1.14 (PB2)
TANK_LOW: R23.2, R24.1, U1.13 (PB1)
VIN: F1.1, J1.1
VIN_F: D3.1 (A1), F1.2, Q3.3 (D)

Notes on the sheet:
12 V INPUT: jack, PTC, TVS, reverse-polarity PMOS
5 V REGULATOR
MCU: ATmega328P-AU, 8 MHz internal
PUMP DRIVER (12 V DC, low voltage only): logic-level NMOS, flyback diode, terminal
AC-EXCITED WATER PROBES: common drive through 1 k, each sense 10 k series, 100 k pull-down
ALARM, STATUS, PROGRAMMING
Jal-Rakshak LOW-VOLTAGE prototype board (never mains). 12 V DC in through PTC, TVS and reverse-polarity PMOS;
AMS1117-5.0 for logic. The probe common electrode is driven by D7 through 1 k; a probe reads wet only if its
sense pin follows the drive HIGH and LOW (AC excitation, no electrolysis). Pump: 12 V DC mini pump up to 1 A
on J5, low-side AO3400A with SS14 flyback. Status LED on D13 and active buzzer on D12 share the ISP lines as
on an Arduino Nano. Firmware: products/04-jal-rakshak/firmware (8 MHz build).
